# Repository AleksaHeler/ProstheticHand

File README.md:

# OpenHand
 
Our attempt at a prosthetic hand controlled by muscle EMG sensors, using linear actuators to move mechanically linked fingers. Implementing our own 3D models (ME), schematic & PCB design of main control board (EE) and software solution (SW).

## Proof of concept

Our (actually second) proof of concept, is using our own PCBs with STM32, our own mechanical design, and some basic software running on STM32 reacting on button press or EMG sensor activation.

For now, this approach seems promising, and only thing left to be changed is the motors used. We use linear actuators, which seem to be exactly what we need, but for now they don't have any position feedback. To solve that we will be using motors with built-in encoders in future, and monitoring their position with STM32 HW timer functions for encoders. Preliminary testing for that worked perfectly, we could always know the position of the motor based on the encoder value, and using endstops we can also calibrate the travel, and using current limiting H bridge motor drivers, we can control the force applied. 

Here are some screenshots of the current status:

### Finger design. Completely mechanical linkage, with linear actuator

### Our custom PCB, with many components including EMG sensors, H bridge motor drivers, etc.

### Also some EMG sensor readings (before additional filtering)

### Now, the whole prototype of the hand (3D printed, batteries, PCB, 3x fingers with motors)

## Example videos of OpenHand in action

Here are some videos of the project for now. Nice to see it finally come together, although this is still early in development, and some things will be changed, and a lot of things will be made to look even prettier.

Note: you might have to download .mp4 videos if GitHub doesn't support playback in browser.

### Showing the response when EMG reading muscle activity 

### Simple demonstration of holding a bottle

### Demo: holding a can of soda

### Demo: holding a multimeter

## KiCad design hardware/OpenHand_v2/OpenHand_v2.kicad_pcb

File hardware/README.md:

# Hardware & PCB designs of the prosthetic hand project

For designing those we use [KiCAD](https://www.kicad.org/download/). Good tutorial can be found [here](https://www.youtube.com/playlist?list=PL3bNyZYHcRSUhUXUt51W6nKvxx2ORvUQB). Although it's for a bit older version of the KiCAD it is still usefull.

For now we have two designs: DevBoard and OpenHand. First one is for proof of concept, while other one is still in development and meant to be used as initial version to build upon.

## DevBoard

Firstly we haver here a development board, custom made for our purpose of having EMG sensors and servo motors connected. Also a couple of buttons/pots etc. for easier debugging/testing. Schematic can be found [here](DevBoard/schematic.pdf).

We will be using [ESP32 S3](https://api.riot-os.org/group__cpu__esp32__esp32s3.html). So in this desin, we're using the ESP32 S3 devboard, but later on we will just use the ESP32 microprocessor.

The boards will be ordered from an online PCB manufacturer, in our case JLC PCB.

DevBoard features:
 - battery/power supply connector
 - 3x servo connectors (with current sensing over 0.1 ohm shunts, and filter for current sensing signal as it is a bit noisy)
 - 2x EMG sensor connectors (signal goes trough RC low-pass filter on its way to the uC)
 - 4x dip switches for easy configuration (easily change code logic on-the go, without re-flashing the board)
 - 2x push buttons (with on-board pullups and HW debounce filter)
 - 2x trim pots and one 'normal' potentiometer (with RC low-pass filter to get rid of some noise from cheap pots)
 - 2x debug LEDs (red/green)
 - 5V regulator for the ESP32 DevBoard
 - input/battery voltage sensing
 - reverse protection diode (would be nice to upgrade to a 'smarter' variant with MOSFET later)
 - 2 layer PCB, components on one side, mix of SMD/THT components
 - a lot of test point pads on the board for all the signals

For now, this DevBoard should give us enough functionality to make some version of a working prototype, but the wishlist for the actual PCB will be updated as we come across new stuff.

### Devboard pictures

#### Schematic

#### PCB design

#### Manufactured PCB

#### Assembled PCB

### Devboard testing

#### Smoke test

When powered from a 12V power supply, the board turns on, power LED is on, nothing caught fire, microcontrollers LED flashing, debug LED flashing (as defined in code). 5V regulator (LM7805) is giving us 5V.

#### Filter testing: EMG sensor

Filter is working. On a screenshot below, channel 1 is raw signal from signal generator which we feed into EMG sensor input, and channel 2 is measured on testpoint for EMG input on the microcontroller. We have a two stage RC low-pass filter with values 10kOhm and 1uF (see shemcatic sheet 1).

#### Filter testing: Servo current

Servo motor current raw signal is looking quite awful:

Here is an example where I connected an external supply to push 1A trough the shunt resistor. Chn 1 is raw, chn 2 is filtered. We can see its filtering enough for now.

#### Filter testing: Button debounce

Similar to EMG sensor, here we see channel 1 is raw button signal, and channel 2 is filtered. We can see the filter is doing its job on and filtering the contact bouncing:

#### Filter testing: Pot debounce

I could not get the pot to give us errors (jumping to gnd of supplied voltage), so it seems the pot is good after all. Although during previous testing some pots were getting some pretty wild oscillations just by tapping them.

#### Input voltage divider

With 10V on input from a bench power supply, at battery sense voltage divider we get 9.97V as input, and output at 1.753V measured with multimeter - as expected (from calculation: 1.754V with 4k7 and 1k resistors in divider).

## OpenHand PCB

Work in progress. 

Features:
 - Microcontroller: STM32 or ESP32, still to be decided, will make a version with both of them
 - USB C connector, CH340C USB to UART IC, JTAG for debugging
 - On-board 3 cell battery charger (BMS to be implemented on the battery pack)
 - Switch mode power suplly, to generate 5V high current for motors, and 3.3V lower current for microcontroller and sensors
 - On-board EMG sensor processing (from raw electrode connections)
 - Some user interaction components - trim-pots, debug LEDs, buttons
 - Separate ADC converter over I2C, for battery voltage sensing and hall effect sensors
 - Hall effect sensors for detecting finger position
 - Input reverse polarity protection with MOSFETs
 - Connectors and drivers (separate motor driver IC) for linear actuators instead of servo motors (H-bridge)
 - Connectors and drivers for haptic feedback (vibrating motor, similar to a console joystick vibration)

Schematic and project can be found [here in OpenHand folder](OpenHand/OpenHand.kicad_pro).

Schematics for now:

Layou for now:

3D PCB view for now:

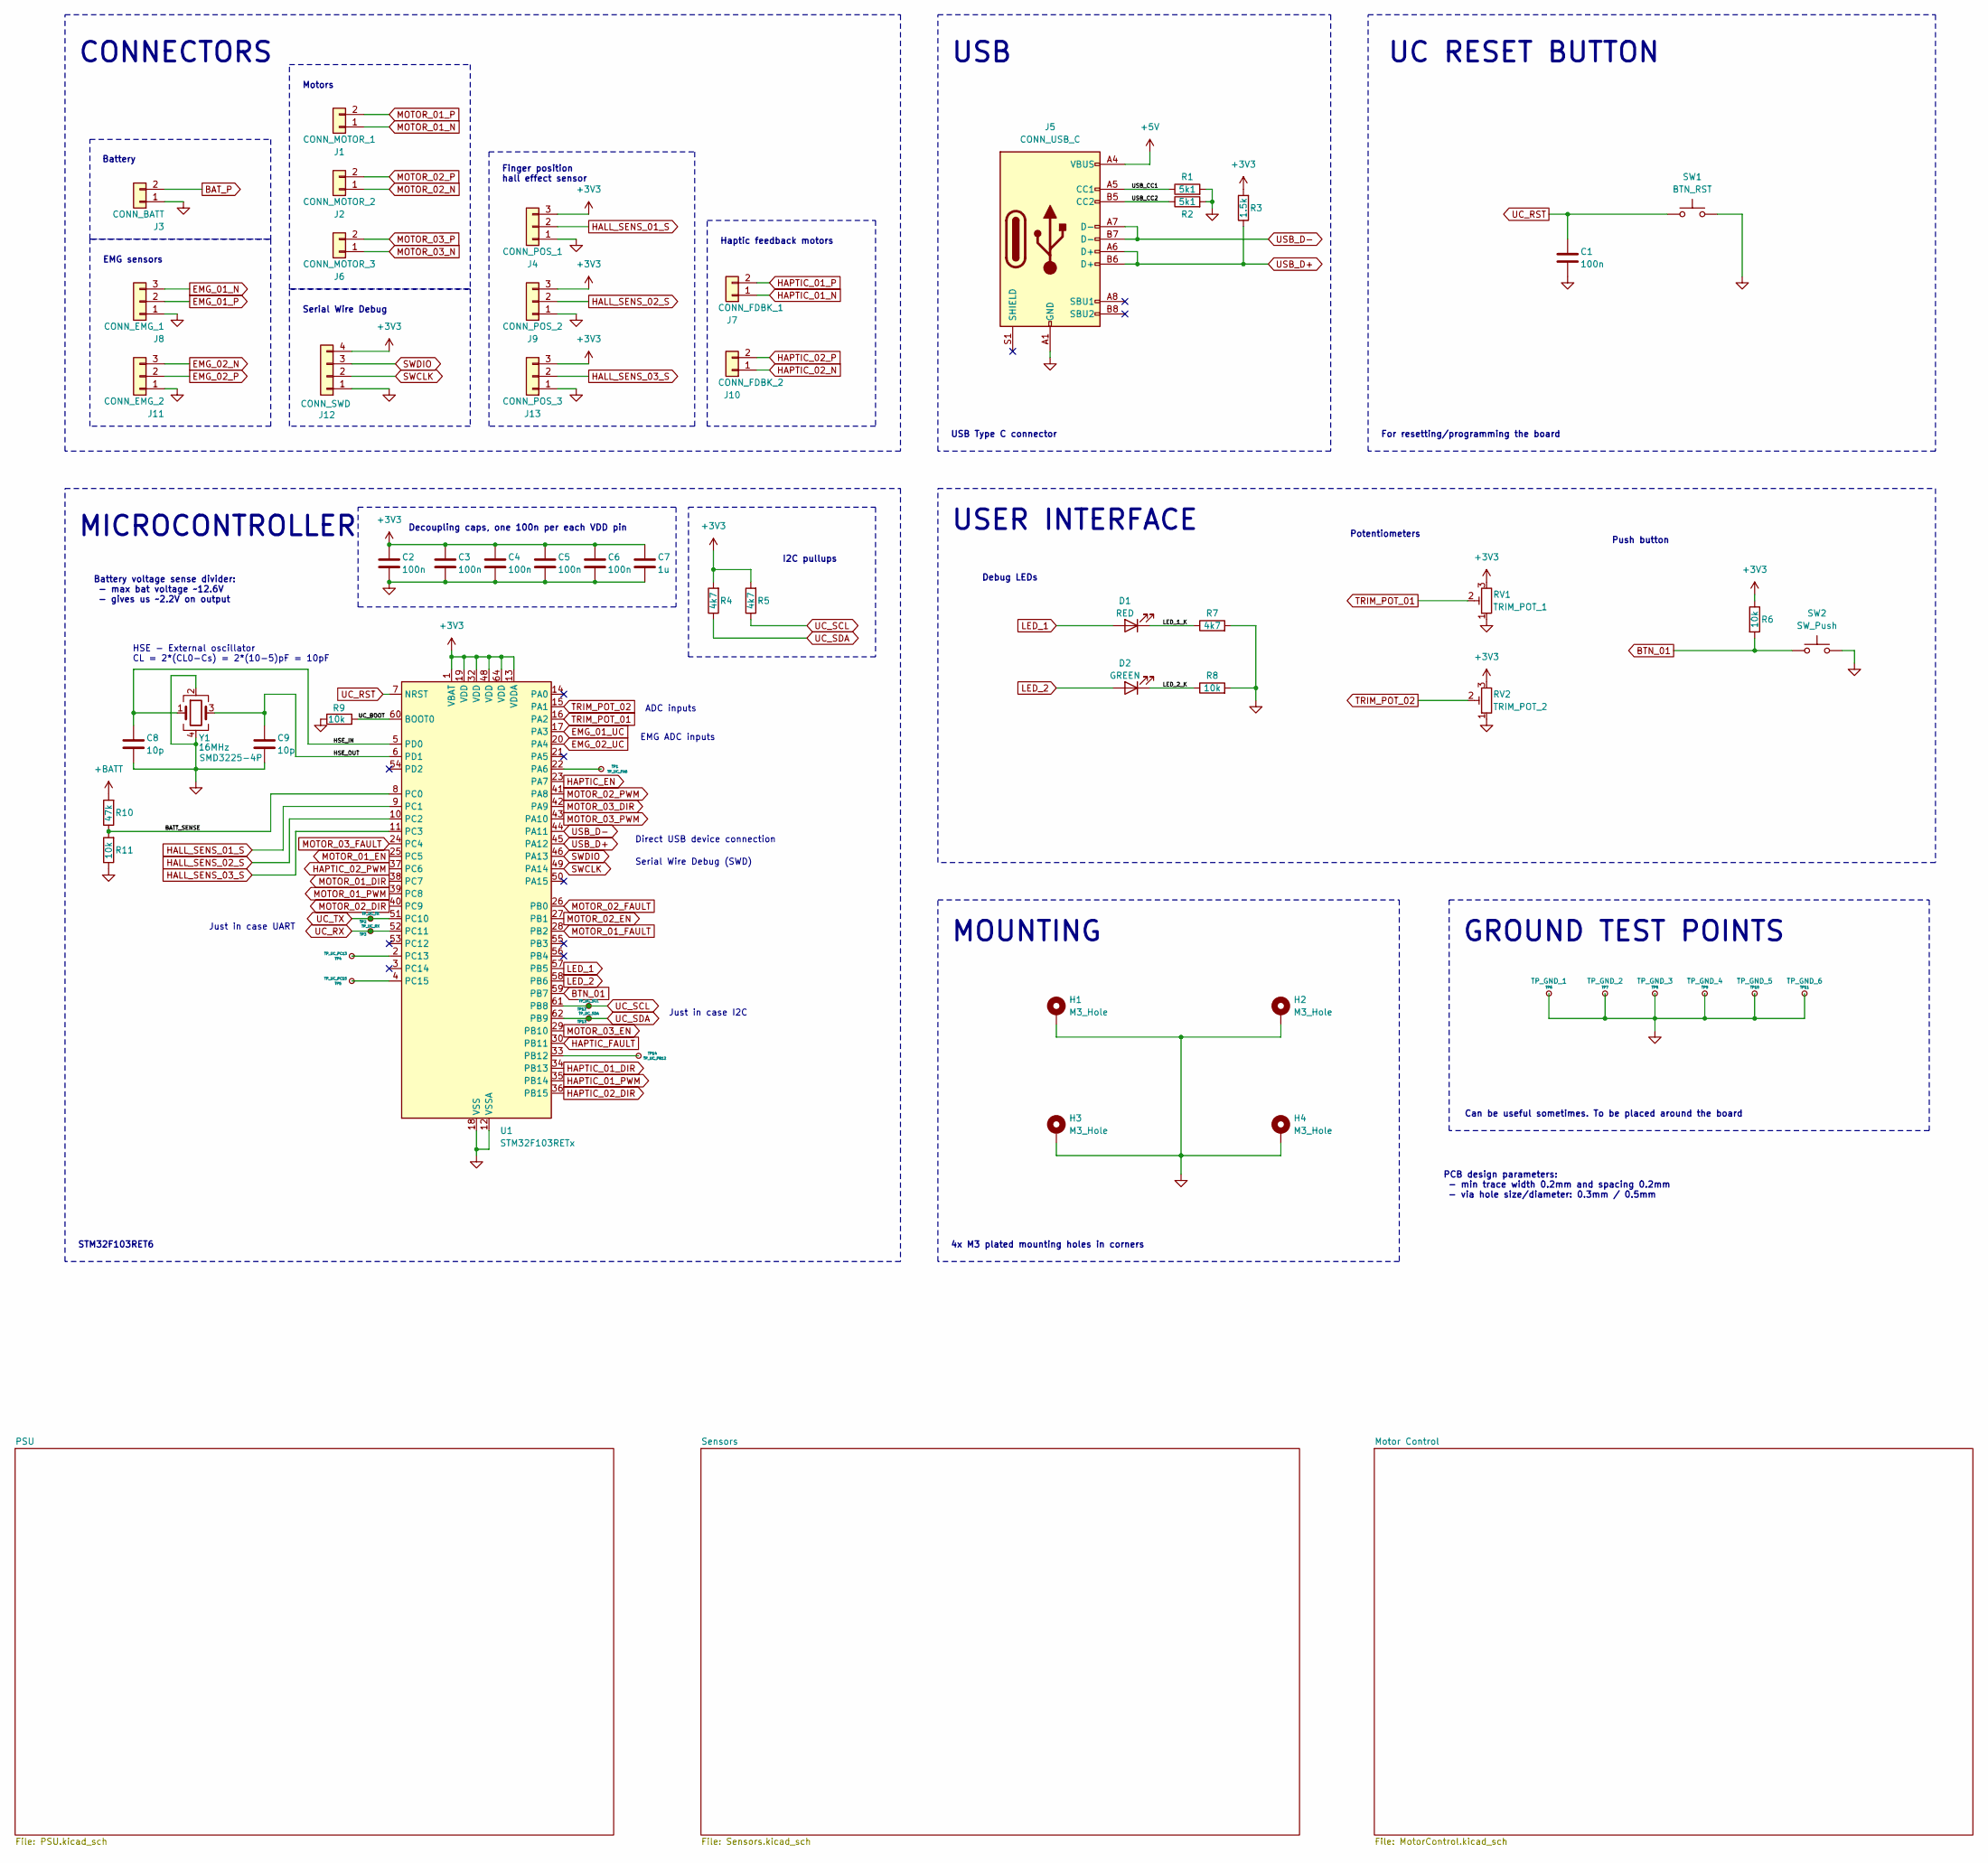
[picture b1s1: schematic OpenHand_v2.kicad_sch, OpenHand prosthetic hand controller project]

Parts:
C1, C2, C3, C4, C5, C6: 100n; C_0805_2012Metric
C7: 1u; C_0805_2012Metric
C8, C9: 10p; C_0805_2012Metric
D1: RED; LED_1210_3225Metric
D2: GREEN; LED_1210_3225Metric
H1, H2, H3, H4: M3_Hole; MountingHole_3.2mm_M3_Pad_Via
J1: CONN_MOTOR_1; JST_EH_S2B-EH_1x02_P2.50mm_Horizontal
J2: CONN_MOTOR_2; JST_EH_S2B-EH_1x02_P2.50mm_Horizontal
J3: CONN_BATT; JST_EH_S2B-EH_1x02_P2.50mm_Horizontal
J4: CONN_POS_1; PinHeader_1x03_P2.54mm_Vertical
J5: CONN_USB_C; USB_C_Receptacle_G-Switch_GT-USB-7010ASV
J6: CONN_MOTOR_3; JST_EH_S2B-EH_1x02_P2.50mm_Horizontal
J7: CONN_FDBK_1; JST_EH_S2B-EH_1x02_P2.50mm_Horizontal
J8: CONN_EMG_1; PinHeader_1x03_P2.54mm_Vertical
J9: CONN_POS_2; PinHeader_1x03_P2.54mm_Vertical
J10: CONN_FDBK_2; JST_EH_S2B-EH_1x02_P2.50mm_Horizontal
J11: CONN_EMG_2; PinHeader_1x03_P2.54mm_Vertical
J12: CONN_SWD; PinHeader_1x04_P2.54mm_Vertical
J13: CONN_POS_3; PinHeader_1x03_P2.54mm_Vertical
R1, R2: 5k1; R_0805_2012Metric
R3: 1.5k; R_0805_2012Metric
R4, R5, R7: 4k7; R_0805_2012Metric
R6, R8, R9, R11: 10k; R_0805_2012Metric
R10: 47k; R_0805_2012Metric
RV1: TRIM_POT_1; Potentiometer_Vishay_TS53YJ_Vertical
RV2: TRIM_POT_2; Potentiometer_Vishay_TS53YJ_Vertical
SW1: BTN_RST; SW_Tactile_SPST_NO_Straight_CK_PTS636Sx25SMTRLFS
SW2: SW_Push; SW_Tactile_SPST_NO_Straight_CK_PTS636Sx25SMTRLFS
TP1: TP_UC_PA6; TestPoint_Pad_D1.0mm
TP2: TP_UC_TX; TestPoint_Pad_D2.0mm
TP3: TP_UC_RX; TestPoint_Pad_D2.0mm
TP4: TP_UC_PC13; TestPoint_Pad_D1.0mm
TP5: TP_UC_PC15; TestPoint_Pad_D1.0mm
TP6: TP_GND_1; TestPoint_Pad_1.5x1.5mm
TP7: TP_GND_2; TestPoint_Pad_1.5x1.5mm
TP8: TP_GND_3; TestPoint_Pad_1.5x1.5mm
TP9: TP_GND_4; TestPoint_Pad_1.5x1.5mm
TP10: TP_GND_5; TestPoint_Pad_1.5x1.5mm
TP11: TP_GND_6; TestPoint_Pad_1.5x1.5mm
TP12: TP_UC_SCL; TestPoint_Pad_D2.0mm
TP13: TP_UC_SDA; TestPoint_Pad_D2.0mm
TP14: TP_UC_PB12; TestPoint_Pad_D1.0mm
U1: STM32F103RETx; LQFP-64_10x10mm_P0.5mm
Y1: 16MHz; Crystal_SMD_3225-4Pin_3.2x2.5mm

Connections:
+3V3: C2.1, C3.1, C4.1, C5.1, C6.1, C7.1, J4.3, J9.3, J12.4, J13.3, R3.2, R4.2, R5.2, R6.1, RV1.3, RV2.3, U1.1 (VBAT), U1.13 (VDDA), U1.19 (VDD), U1.32 (VDD), U1.48 (VDD), U1.64 (VDD); also elsewhere on the board
+5V: J5.A4 (VBUS), J5.A9 (VBUS), J5.B4 (VBUS), J5.B9 (VBUS); also elsewhere on the board
+BATT: R10.2; also elsewhere on the board
/BATT_SENSE: R10.1, R11.2, U1.8 (PC0)
/HSE_IN: C8.1, U1.5 (PD0), Y1.1
/HSE_OUT: C9.1, U1.6 (PD1), Y1.3
/LED_1_K: D1.1 (K), R7.1
/LED_2_K: D2.1 (K), R8.1
/UC_BOOT: R9.2, U1.60 (BOOT0)
/USB_CC1: J5.A5 (CC1), R1.1
/USB_CC2: J5.B5 (CC2), R2.1
BAT_P: J3.2; also elsewhere on the board
BTN_01: R6.2, SW2.1, U1.59 (PB7)
EMG_01_N: J8.3; also elsewhere on the board
EMG_01_P: J8.2; also elsewhere on the board
EMG_01_UC: U1.17 (PA3); also elsewhere on the board
EMG_02_N: J11.3; also elsewhere on the board
EMG_02_P: J11.2; also elsewhere on the board
EMG_02_UC: U1.20 (PA4); also elsewhere on the board
GND: C1.2, C2.2, C3.2, C4.2, C5.2, C6.2, C7.2, C8.2, C9.2, H1.1, H2.1, H3.1, H4.1, J3.1, J4.1, J5.A1 (GND), J5.A12 (GND), J5.B1 (GND), J5.B12 (GND), J8.1, J9.1, J11.1, J12.1, J13.1, R1.2, R2.2, R7.2, R8.2, R9.1, R11.1, RV1.1, RV2.1, SW1.2, SW2.2, TP6.1, TP7.1, TP8.1, TP9.1, TP10.1, TP11.1, U1.12 (VSSA), U1.18 (VSS), U1.31 (VSS), U1.47 (VSS), U1.63 (VSS), Y1.2, Y1.4; also elsewhere on the board
HALL_SENS_01_S: J4.2, U1.9 (PC1)
HALL_SENS_02_S: J9.2, U1.10 (PC2)
HALL_SENS_03_S: J13.2, U1.11 (PC3)
HAPTIC_01_DIR: U1.34 (PB13); also elsewhere on the board
HAPTIC_01_N: J7.1; also elsewhere on the board
HAPTIC_01_P: J7.2; also elsewhere on the board
HAPTIC_01_PWM: U1.35 (PB14); also elsewhere on the board
HAPTIC_02_DIR: U1.36 (PB15); also elsewhere on the board
HAPTIC_02_N: J10.1; also elsewhere on the board
HAPTIC_02_P: J10.2; also elsewhere on the board
HAPTIC_02_PWM: U1.37 (PC6); also elsewhere on the board
HAPTIC_EN: U1.23 (PA7); also elsewhere on the board
HAPTIC_FAULT: U1.30 (PB11); also elsewhere on the board
LED_1: D1.2 (A), U1.57 (PB5)
LED_2: D2.2 (A), U1.58 (PB6)
MOTOR_01_DIR: U1.38 (PC7); also elsewhere on the board
MOTOR_01_EN: U1.25 (PC5); also elsewhere on the board
MOTOR_01_FAULT: U1.28 (PB2); also elsewhere on the board
MOTOR_01_N: J1.1; also elsewhere on the board
MOTOR_01_P: J1.2; also elsewhere on the board
MOTOR_01_PWM: U1.39 (PC8); also elsewhere on the board
MOTOR_02_DIR: U1.40 (PC9); also elsewhere on the board
MOTOR_02_EN: U1.27 (PB1); also elsewhere on the board
MOTOR_02_FAULT: U1.26 (PB0); also elsewhere on the board
MOTOR_02_N: J2.1; also elsewhere on the board
MOTOR_02_P: J2.2; also elsewhere on the board
MOTOR_02_PWM: U1.41 (PA8); also elsewhere on the board
MOTOR_03_DIR: U1.42 (PA9); also elsewhere on the board
MOTOR_03_EN: U1.29 (PB10); also elsewhere on the board
MOTOR_03_FAULT: U1.24 (PC4); also elsewhere on the board
MOTOR_03_N: J6.1; also elsewhere on the board
MOTOR_03_P: J6.2; also elsewhere on the board
MOTOR_03_PWM: U1.43 (PA10); also elsewhere on the board
unnamed: TP1.1, U1.22 (PA6)
unnamed: TP14.1, U1.33 (PB12)
unnamed: TP4.1, U1.2 (PC13)
unnamed: TP5.1, U1.4 (PC15)
SWCLK: J12.2, U1.49 (PA14)
SWDIO: J12.3, U1.46 (PA13)
TRIM_POT_01: RV1.2, U1.16 (PA2)
TRIM_POT_02: RV2.2, U1.15 (PA1)
UC_RST: C1.1, SW1.1, U1.7 (NRST)
UC_RX: TP3.1, U1.52 (PC11)
UC_SCL: R5.1, TP12.1, U1.61 (PB8)
UC_SDA: R4.1, TP13.1, U1.62 (PB9)
UC_TX: TP2.1, U1.51 (PC10)
USB_D+: J5.A6 (D+), J5.B6 (D+), R3.1, U1.45 (PA12)
USB_D-: J5.A7 (D-), J5.B7 (D-), U1.44 (PA11)

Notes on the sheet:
I2C pullups
Debug LEDs
UC RESET BUTTON
Potentiometers
Serial Wire Debug (SWD)
MICROCONTROLLER
Battery
EMG ADC inputs
Just in case I2C
Haptic feedback motors
USB
Push button
4x M3 plated mounting holes in corners
Battery voltage sense divider: - max bat voltage ~12.6V - gives us ~2.2V on output
ADC inputs
Motors
MOUNTING
CONNECTORS
PCB design parameters: - min trace width 0.2mm and spacing 0.2mm - via hole size/diameter: 0.3mm / 0.5mm
For resetting/programming the board
HSE - External oscillator CL = 2*(CL0-Cs) = 2*(10-5)pF = 10pF
Can be useful sometimes. To be placed around the board
USB Type C connector
Decoupling caps, one 100n per each VDD pin
USER INTERFACE
STM32F103RET6
Finger position hall effect sensor
GROUND TEST POINTS
Just in case UART
EMG sensors
Direct USB device connection
Serial Wire Debug

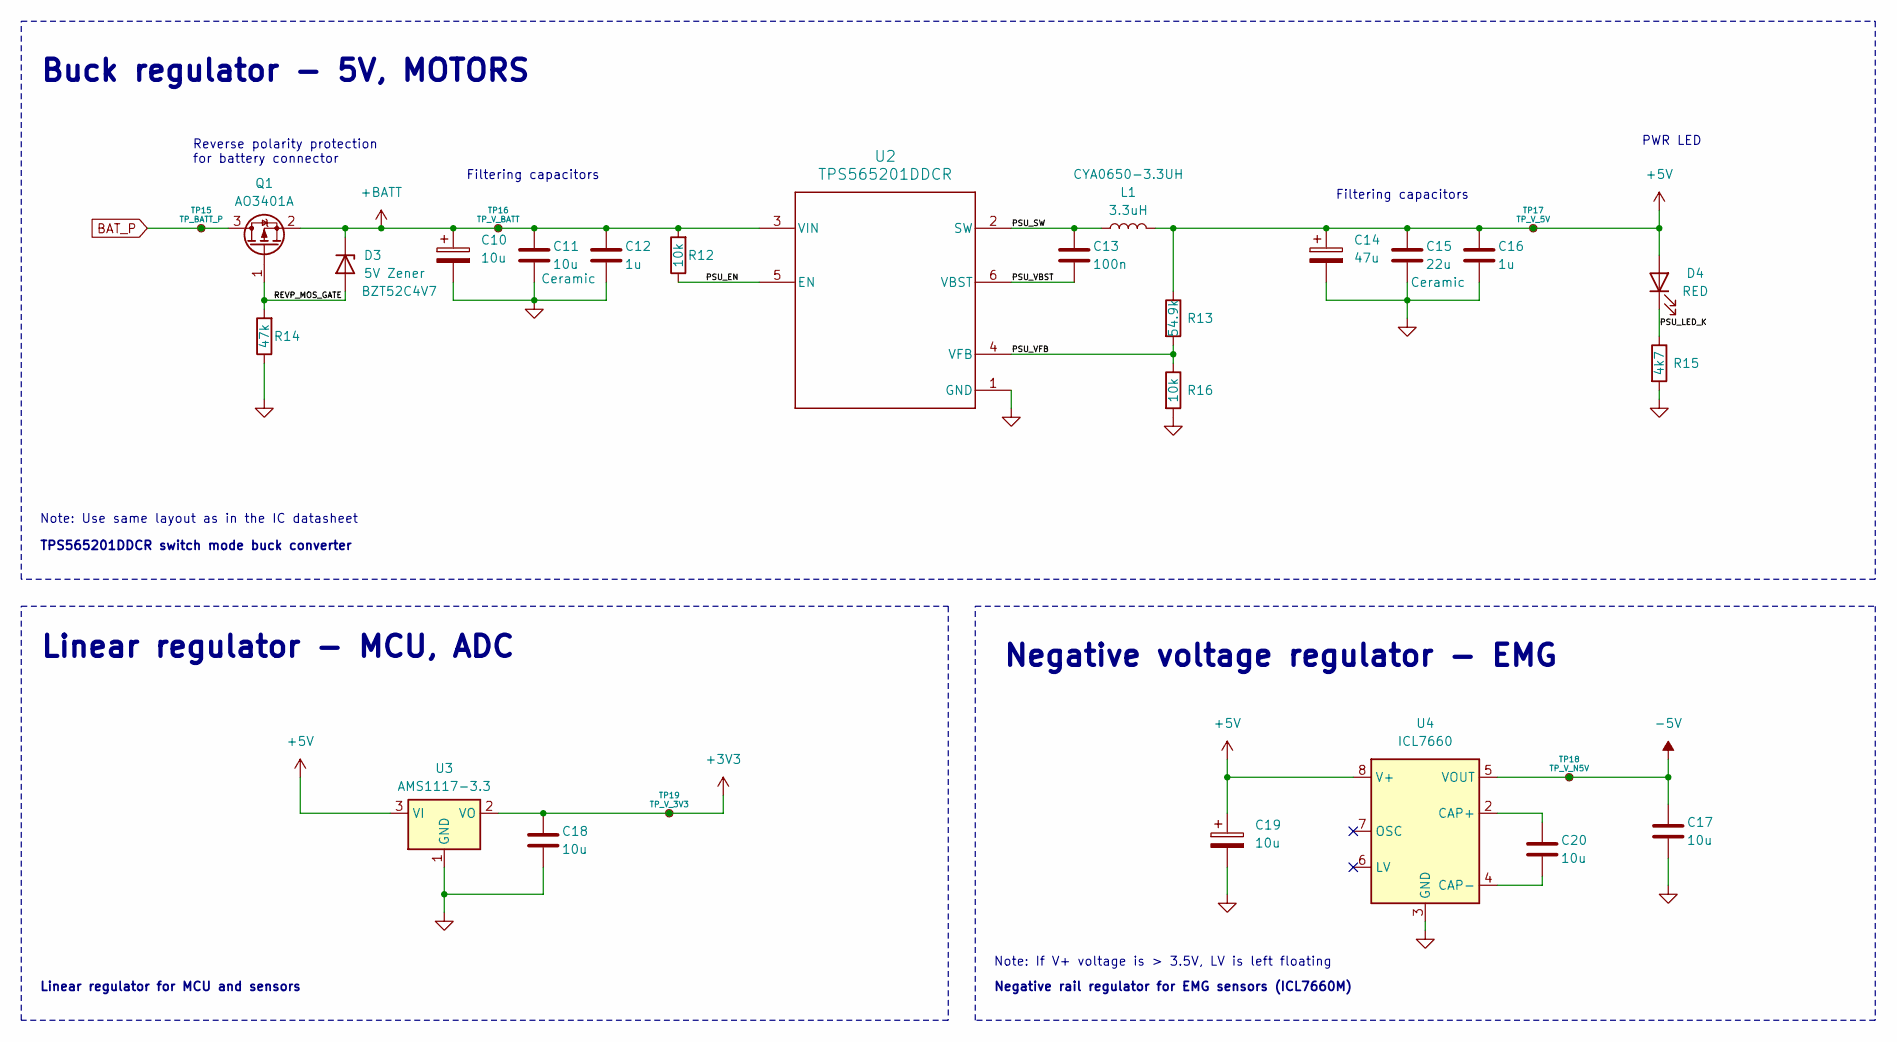
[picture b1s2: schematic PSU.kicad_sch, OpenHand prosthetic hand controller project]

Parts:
C10, C19: 10u; CP_Elec_4x5.4
C11, C17, C18, C20: 10u; C_0805_2012Metric
C12, C16: 1u; C_0805_2012Metric
C13: 100n; C_0805_2012Metric
C14: 47u; CP_Elec_6.3x5.4
C15: 22u; C_0805_2012Metric
D3: 5V Zener; D_SOD-123; Part Number BZT52C4V7
D4: RED; LED_1210_3225Metric
L1: 3.3uH; L_Bourns_SRP7028A_7.3x6.6mm; Part Number CYA0650-3.3UH
Q1: AO3401A; SOT-23
R12, R16: 10k; R_0805_2012Metric
R13: 54.9k; R_0805_2012Metric
R14: 47k; R_0805_2012Metric
R15: 4k7; R_0805_2012Metric
TP15: TP_BATT_P; TestPoint_Pad_D1.0mm
TP16: TP_V_BATT; TestPoint_Pad_D1.0mm
TP17: TP_V_5V; TestPoint_Pad_D2.0mm
TP18: TP_V_N5V; TestPoint_Pad_D2.0mm
TP19: TP_V_3V3; TestPoint_Pad_D2.0mm
U2: TPS565201DDCR; TPS565201DDCR_L
U3: AMS1117-3.3; SOT-223-3_TabPin2
U4: ICL7660; SOP-8_3.9x4.9mm_P1.27mm

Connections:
+3V3: C18.1, TP19.1, U3.2 (VO); also elsewhere on the board
+5V: C14.1, C15.1, C16.1, C19.1, D4.2 (A), L1.2, R13.1, TP17.1, U3.3 (VI), U4.8 (V+); also elsewhere on the board
+BATT: C10.1, C11.1, C12.1, D3.1 (K), Q1.2 (S), R12.2, TP16.1, U2.3 (VIN); also elsewhere on the board
-5V: C17.1, TP18.1, U4.5 (VOUT); also elsewhere on the board
/PSU/PSU_EN: R12.1, U2.5 (EN)
/PSU/PSU_LED_K: D4.1 (K), R15.1
/PSU/PSU_SW: C13.1, L1.1, U2.2 (SW)
/PSU/PSU_VBST: C13.2, U2.6 (VBST)
/PSU/PSU_VFB: R13.2, R16.1, U2.4 (VFB)
/PSU/REVP_MOS_GATE: D3.2 (A), Q1.1 (G), R14.2
BAT_P: Q1.3 (D), TP15.1; also elsewhere on the board
GND: C10.2, C11.2, C12.2, C14.2, C15.2, C16.2, C17.2, C18.2, C19.2, R14.1, R15.2, R16.2, U2.1 (GND), U3.1 (GND), U4.3 (GND); also elsewhere on the board
unnamed: C20.1, U4.2 (CAP+)
unnamed: C20.2, U4.4 (CAP-)

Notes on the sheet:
Linear regulator - MCU, ADC
Note: Use same layout as in the IC datasheet
Filtering capacitors
PWR LED
Note: If V+ voltage is > 3.5V, LV is left floating
Negative voltage regulator - EMG
Buck regulator - 5V, MOTORS
TPS565201DDCR switch mode buck converter
Negative rail regulator for EMG sensors (ICL7660M)
Linear regulator for MCU and sensors
Reverse polarity protection for battery connector

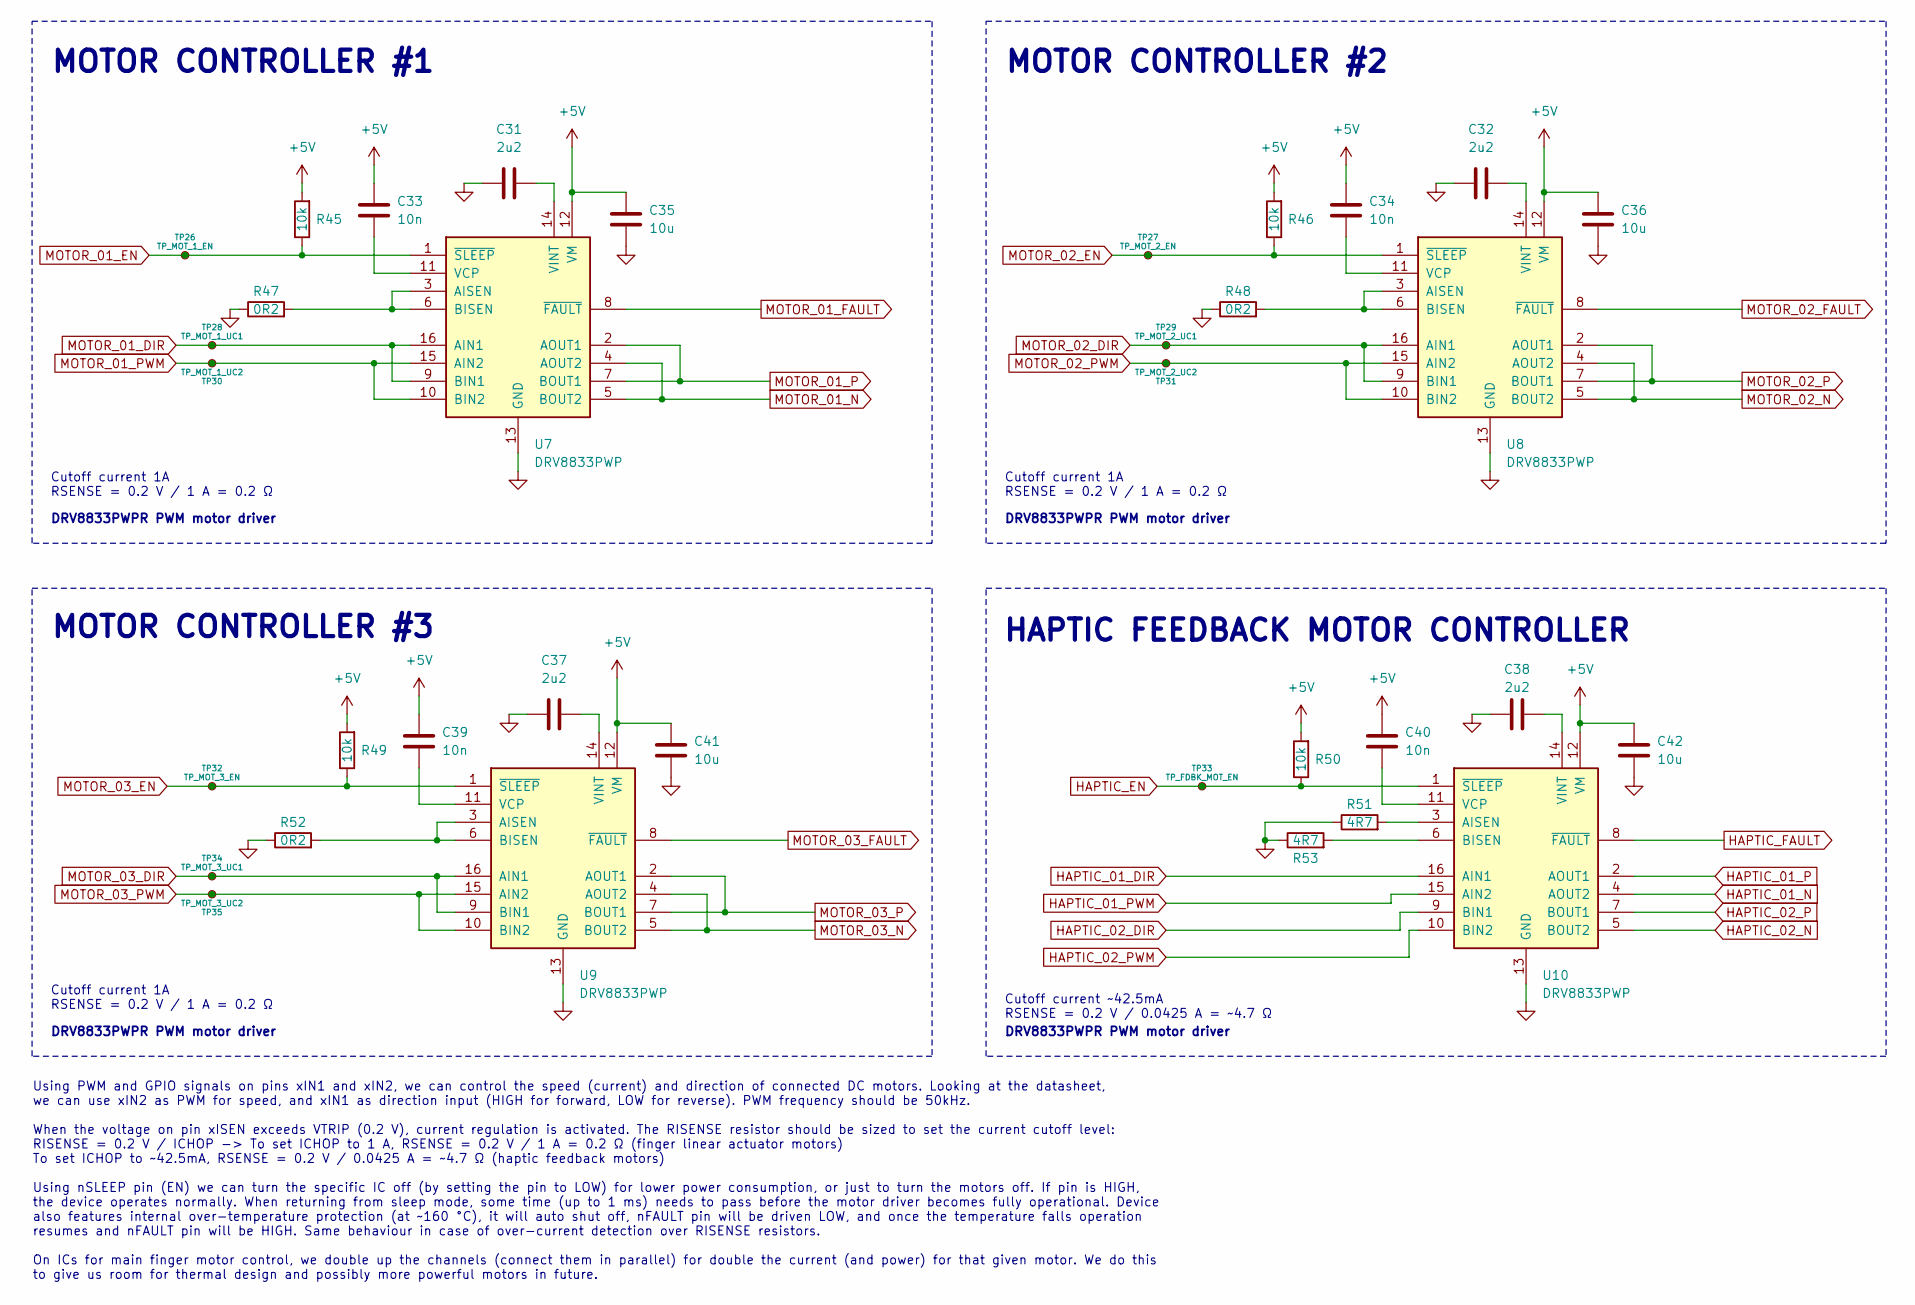
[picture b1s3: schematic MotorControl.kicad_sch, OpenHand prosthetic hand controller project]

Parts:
C31, C32, C37, C38: 2u2; C_0805_2012Metric
C33, C34, C39, C40: 10n; C_0805_2012Metric
C35, C36, C41, C42: 10u; C_0805_2012Metric
R45, R46, R49, R50: 10k; R_0805_2012Metric
R47, R48, R52: 0R2; R_1206_3216Metric
R51, R53: 4R7; R_1206_3216Metric
TP26: TP_MOT_1_EN; TestPoint_Pad_D1.0mm
TP27: TP_MOT_2_EN; TestPoint_Pad_D1.0mm
TP28: TP_MOT_1_UC1; TestPoint_Pad_D1.0mm
TP29: TP_MOT_2_UC1; TestPoint_Pad_D1.0mm
TP30: TP_MOT_1_UC2; TestPoint_Pad_D1.0mm
TP31: TP_MOT_2_UC2; TestPoint_Pad_D1.0mm
TP32: TP_MOT_3_EN; TestPoint_Pad_D1.0mm
TP33: TP_FDBK_MOT_EN; TestPoint_Pad_D1.0mm
TP34: TP_MOT_3_UC1; TestPoint_Pad_D1.0mm
TP35: TP_MOT_3_UC2; TestPoint_Pad_D1.0mm
U7, U8, U9, U10: DRV8833PWP; HTSSOP-16-1EP_4.4x5mm_P0.65mm_EP3.4x5mm_Mask2.46x2.31mm_The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

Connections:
+5V: C33.1, C34.1, C35.1, C36.1, C39.1, C40.1, C41.1, C42.1, R45.2, R46.2, R49.2, R50.2, U7.12 (VM), U8.12 (VM), U9.12 (VM), U10.12 (VM); also elsewhere on the board
GND: C31.1, C32.1, C35.2, C36.2, C37.1, C38.1, C41.2, C42.2, R47.1, R48.1, R51.1, R52.1, R53.1, U7.13 (GND), U7.17 (GND), U8.13 (GND), U8.17 (GND), U9.13 (GND), U9.17 (GND), U10.13 (GND), U10.17 (GND); also elsewhere on the board
HAPTIC_01_DIR: U10.16 (AIN1); also elsewhere on the board
HAPTIC_01_N: U10.4 (AOUT2); also elsewhere on the board
HAPTIC_01_P: U10.2 (AOUT1); also elsewhere on the board
HAPTIC_01_PWM: U10.15 (AIN2); also elsewhere on the board
HAPTIC_02_DIR: U10.9 (BIN1); also elsewhere on the board
HAPTIC_02_N: U10.5 (BOUT2); also elsewhere on the board
HAPTIC_02_P: U10.7 (BOUT1); also elsewhere on the board
HAPTIC_02_PWM: U10.10 (BIN2); also elsewhere on the board
HAPTIC_EN: R50.1, TP33.1, U10.1 (~SLEEP); also elsewhere on the board
HAPTIC_FAULT: U10.8 (~FAULT); also elsewhere on the board
MOTOR_01_DIR: TP28.1, U7.9 (BIN1), U7.16 (AIN1); also elsewhere on the board
MOTOR_01_EN: R45.1, TP26.1, U7.1 (~SLEEP); also elsewhere on the board
MOTOR_01_FAULT: U7.8 (~FAULT); also elsewhere on the board
MOTOR_01_N: U7.4 (AOUT2), U7.5 (BOUT2); also elsewhere on the board
MOTOR_01_P: U7.2 (AOUT1), U7.7 (BOUT1); also elsewhere on the board
MOTOR_01_PWM: TP30.1, U7.10 (BIN2), U7.15 (AIN2); also elsewhere on the board
MOTOR_02_DIR: TP29.1, U8.9 (BIN1), U8.16 (AIN1); also elsewhere on the board
MOTOR_02_EN: R46.1, TP27.1, U8.1 (~SLEEP); also elsewhere on the board
MOTOR_02_FAULT: U8.8 (~FAULT); also elsewhere on the board
MOTOR_02_N: U8.4 (AOUT2), U8.5 (BOUT2); also elsewhere on the board
MOTOR_02_P: U8.2 (AOUT1), U8.7 (BOUT1); also elsewhere on the board
MOTOR_02_PWM: TP31.1, U8.10 (BIN2), U8.15 (AIN2); also elsewhere on the board
MOTOR_03_DIR: TP34.1, U9.9 (BIN1), U9.16 (AIN1); also elsewhere on the board
MOTOR_03_EN: R49.1, TP32.1, U9.1 (~SLEEP); also elsewhere on the board
MOTOR_03_FAULT: U9.8 (~FAULT); also elsewhere on the board
MOTOR_03_N: U9.4 (AOUT2), U9.5 (BOUT2); also elsewhere on the board
MOTOR_03_P: U9.2 (AOUT1), U9.7 (BOUT1); also elsewhere on the board
MOTOR_03_PWM: TP35.1, U9.10 (BIN2), U9.15 (AIN2); also elsewhere on the board
unnamed: R47.2, U7.3 (AISEN), U7.6 (BISEN)
unnamed: C33.2, U7.11 (VCP)
unnamed: C31.2, U7.14 (VINT)
unnamed: R48.2, U8.3 (AISEN), U8.6 (BISEN)
unnamed: C34.2, U8.11 (VCP)
unnamed: C32.2, U8.14 (VINT)
unnamed: R52.2, U9.3 (AISEN), U9.6 (BISEN)
unnamed: C39.2, U9.11 (VCP)
unnamed: C37.2, U9.14 (VINT)
unnamed: R51.2, U10.3 (AISEN)
unnamed: R53.2, U10.6 (BISEN)
unnamed: C40.2, U10.11 (VCP)
unnamed: C38.2, U10.14 (VINT)

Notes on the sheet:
Cutoff current 1A RSENSE = 0.2 V / 1 A = 0.2 Ω
MOTOR CONTROLLER #1
DRV8833PWPR PWM motor driver
HAPTIC FEEDBACK MOTOR CONTROLLER
Using PWM and GPIO signals on pins xIN1 and xIN2, we can control the speed (current) and direction of connected DC motors. Looking at the datasheet, we can use xIN2 as PWM for speed, and xIN1 as direction input (HIGH for forward, LOW for reverse). PWM frequency should be 50kHz. When the voltage on 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
MOTOR CONTROLLER #3
MOTOR CONTROLLER #2
Cutoff current ~42.5mA RSENSE = 0.2 V / 0.0425 A = ~4.7 Ω

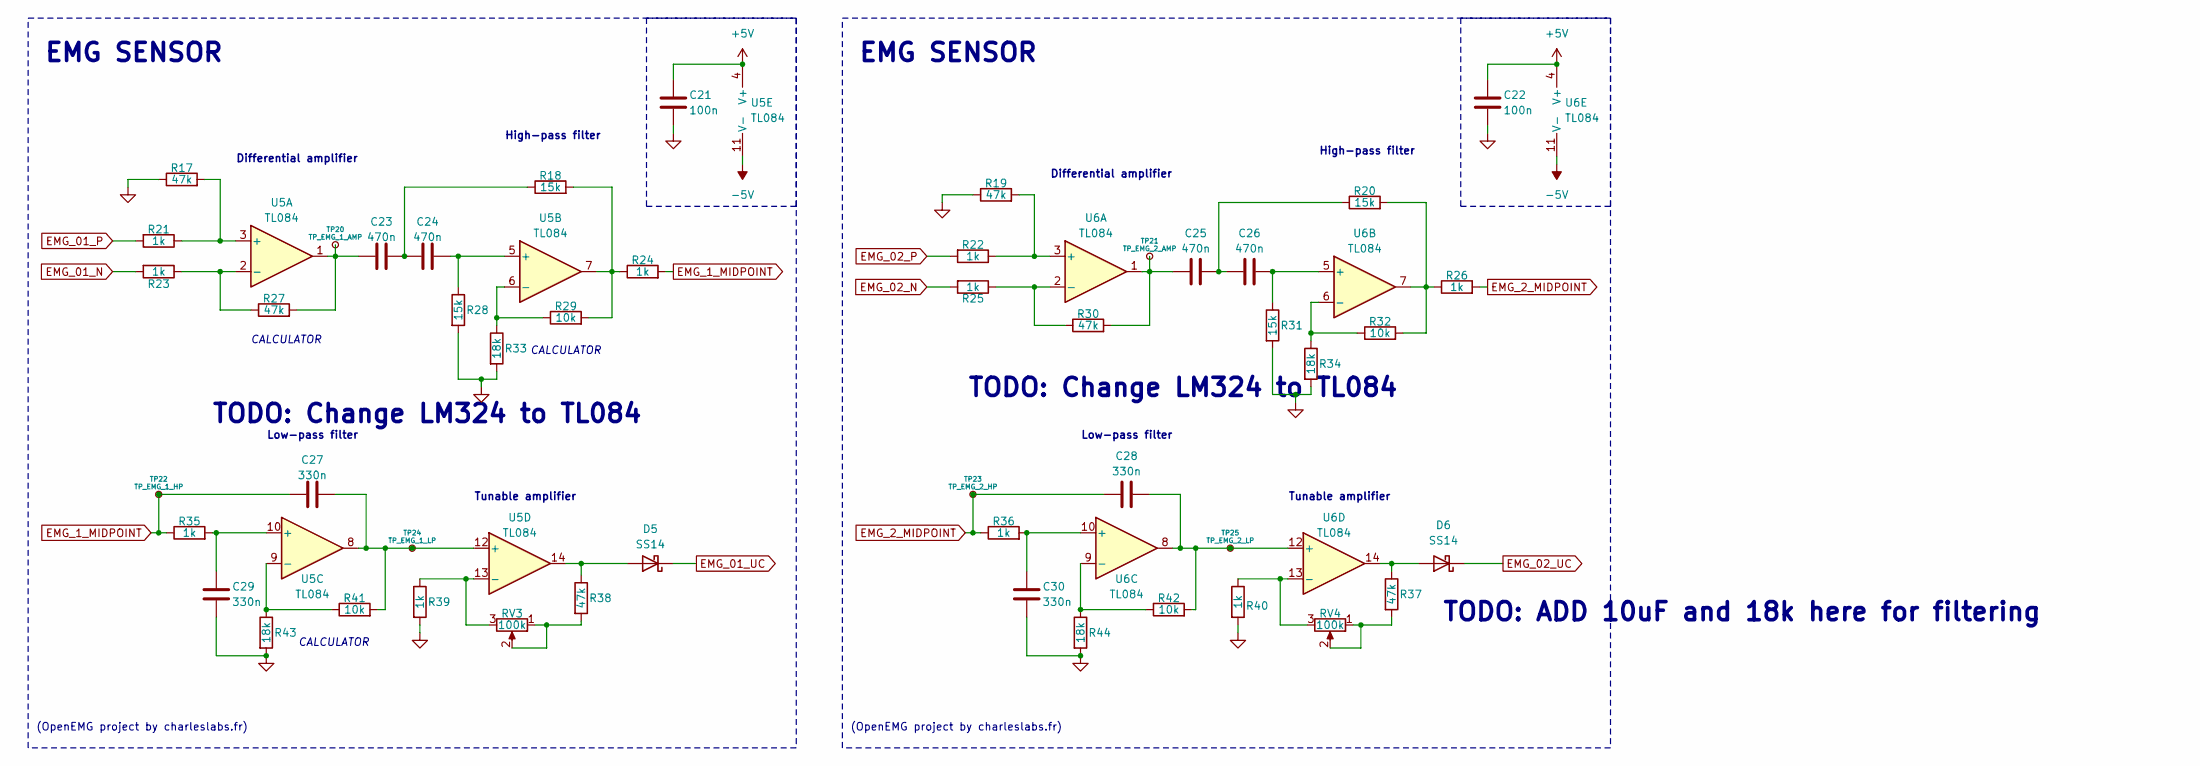
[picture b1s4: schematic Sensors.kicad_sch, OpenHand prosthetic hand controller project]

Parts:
C21, C22: 100n; C_0805_2012Metric
C23, C24, C25, C26: 470n; C_0805_2012Metric
C27, C28, C29, C30: 330n; C_0805_2012Metric
D5, D6: SS14; D_SOD-123
R17, R19, R27, R30, R37, R38: 47k; R_0805_2012Metric
R18, R20, R28, R31: 15k; R_0805_2012Metric
R21, R22, R23, R24, R25, R26, R35, R36, R39, R40: 1k; R_0805_2012Metric
R29, R32, R41, R42: 10k; R_0805_2012Metric
R33, R34, R43, R44: 18k; R_0805_2012Metric
RV3, RV4: 100k; Potentiometer_Vishay_TS53YJ_Vertical
TP20: TP_EMG_1_AMP; TestPoint_Pad_D1.0mm
TP21: TP_EMG_2_AMP; TestPoint_Pad_D1.0mm
TP22: TP_EMG_1_HP; TestPoint_Pad_D1.0mm
TP23: TP_EMG_2_HP; TestPoint_Pad_D1.0mm
TP24: TP_EMG_1_LP; TestPoint_Pad_D1.0mm
TP25: TP_EMG_2_LP; TestPoint_Pad_D1.0mm
U5, U6: TL084; SO-14_5.3x10.2mm_P1.27mm

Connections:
+5V: C21.1, C22.1, U5.4 (V+), U6.4 (V+); also elsewhere on the board
-5V: U5.11 (V-), U6.11 (V-); also elsewhere on the board
EMG_1_MIDPOINT: C27.1, R24.2, R35.1, TP22.1
EMG_01_N: R23.2; also elsewhere on the board
EMG_01_P: R21.2; also elsewhere on the board
EMG_01_UC: D5.1 (K); also elsewhere on the board
EMG_2_MIDPOINT: C28.1, R26.2, R36.1, TP23.1
EMG_02_N: R25.2; also elsewhere on the board
EMG_02_P: R22.2; also elsewhere on the board
EMG_02_UC: D6.1 (K); also elsewhere on the board
GND: C21.2, C22.2, C29.1, C30.1, R17.1, R19.1, R28.2, R31.2, R33.2, R34.2, R39.2, R40.2, R43.2, R44.2; also elsewhere on the board
unnamed: C23.1, R27.2, TP20.1, U5.1
unnamed: C23.2, C24.1, R18.1
unnamed: C25.1, R30.2, TP21.1, U6.1
unnamed: C25.2, C26.1, R20.1
unnamed: D5.2 (A), R38.1, U5.14
unnamed: D6.2 (A), R37.1, U6.14
unnamed: R18.2, R24.1, R29.2, U5.7
unnamed: R20.2, R26.1, R32.2, U6.7
unnamed: R37.2, RV4.1, RV4.2
unnamed: R38.2, RV3.1, RV3.2
unnamed: R17.2, R21.1, U5.3 (+)
unnamed: R23.1, R27.1, U5.2 (-)
unnamed: C24.2, R28.1, U5.5 (+)
unnamed: R29.1, R33.1, U5.6 (-)
unnamed: C29.2, R35.2, U5.10 (+)
unnamed: R41.1, R43.1, U5.9 (-)
unnamed: C27.2, R41.2, TP24.1, U5.8, U5.12 (+)
unnamed: R39.1, RV3.3, U5.13 (-)
unnamed: R19.2, R22.1, U6.3 (+)
unnamed: R25.1, R30.1, U6.2 (-)
unnamed: C26.2, R31.1, U6.5 (+)
unnamed: R32.1, R34.1, U6.6 (-)
unnamed: C30.2, R36.2, U6.10 (+)
unnamed: R42.1, R44.1, U6.9 (-)
unnamed: C28.2, R42.2, TP25.1, U6.8, U6.12 (+)
unnamed: R40.1, RV4.3, U6.13 (-)

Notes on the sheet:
EMG SENSOR
TODO: Change LM324 to TL084
Low-pass filter
CALCULATOR
Differential amplifier
(OpenEMG project by charleslabs.fr)
High-pass filter
Tunable amplifier
TODO: ADD 10uF and 18k here for filtering

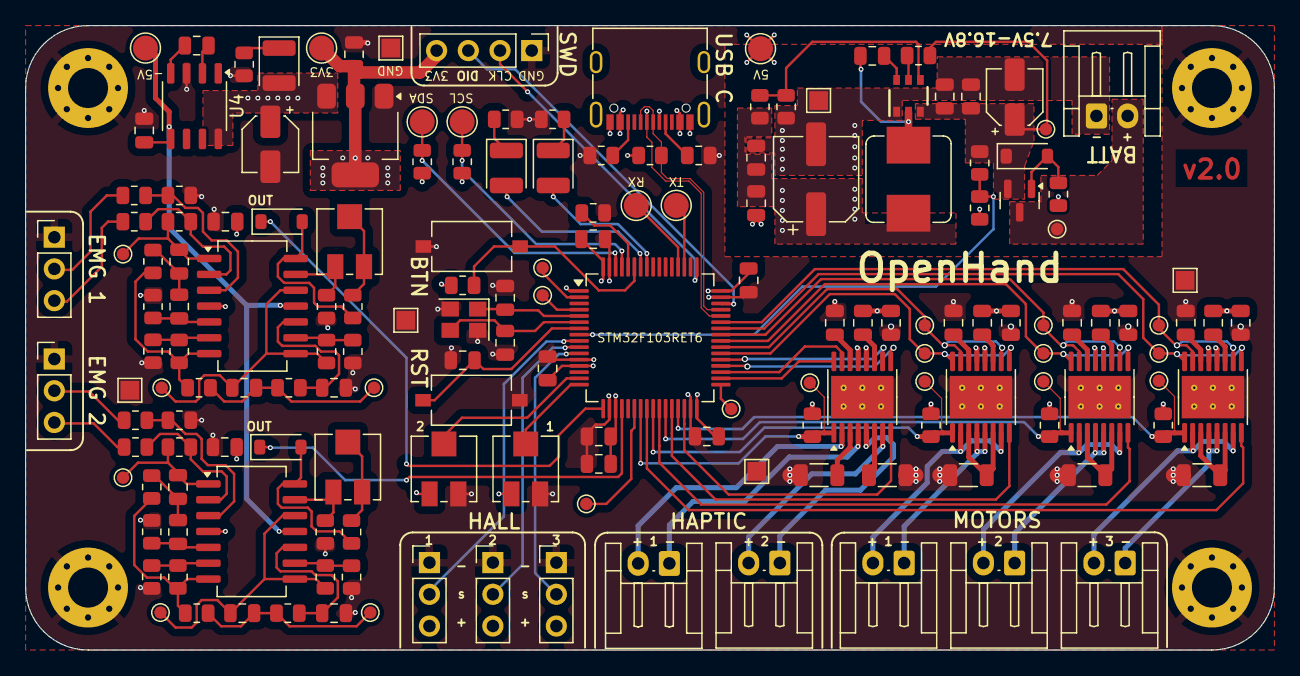
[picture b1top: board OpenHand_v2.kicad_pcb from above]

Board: 4 copper layers, 100.0 x 50.0 mm, 172 parts (0 on the bottom side), 118 nets.

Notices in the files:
hardware/DevelopmentBoard/DevelopmentBoard.kicad_pcb:
creativecommons.org/license/by/4.0
License: CC BY 4.0
hardware/DevelopmentBoard/DevelopmentBoard.kicad_sch:
creativecommons.org/licenses/by/4.0
